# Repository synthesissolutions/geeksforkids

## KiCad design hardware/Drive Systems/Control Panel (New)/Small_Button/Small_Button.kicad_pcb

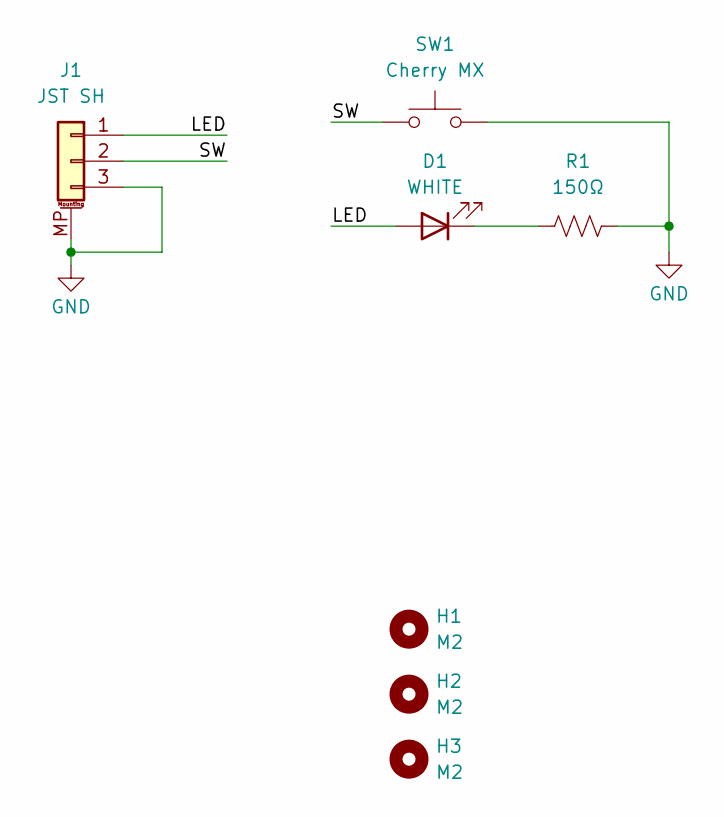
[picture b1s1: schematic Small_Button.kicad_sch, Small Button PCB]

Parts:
D1: WHITE; LED_D3.0mm; MPN C210322
H1, H2, H3: M2; MountingHole_2.2mm_M2_DIN965
J1: JST SH; JST_SH_SM03B-SRSS-TB_1x03-1MP_P1.00mm_Horizontal; MPN C160403
R1: 150Ω; R_0603_1608Metric; MPN C2907103
SW1: Cherry MX; SW_Cherry_MX_1.00u_PCB; MPN C400229

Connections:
/LED: D1.2 (A), J1.1
/SW: J1.2, SW1.1
GND: J1.3, J1.MP (MountPin), R1.2, SW1.2
unnamed: D1.1 (K), R1.1

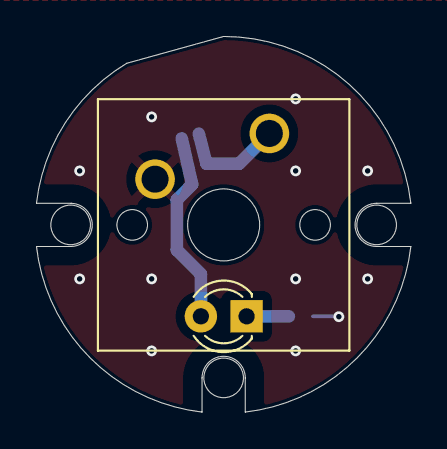
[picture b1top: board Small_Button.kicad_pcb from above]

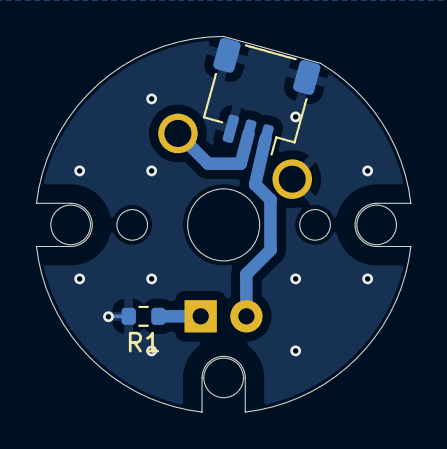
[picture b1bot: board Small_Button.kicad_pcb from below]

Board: 2 copper layers, 20.8 x 20.9 mm, 7 parts (2 on the bottom side), 4 nets.

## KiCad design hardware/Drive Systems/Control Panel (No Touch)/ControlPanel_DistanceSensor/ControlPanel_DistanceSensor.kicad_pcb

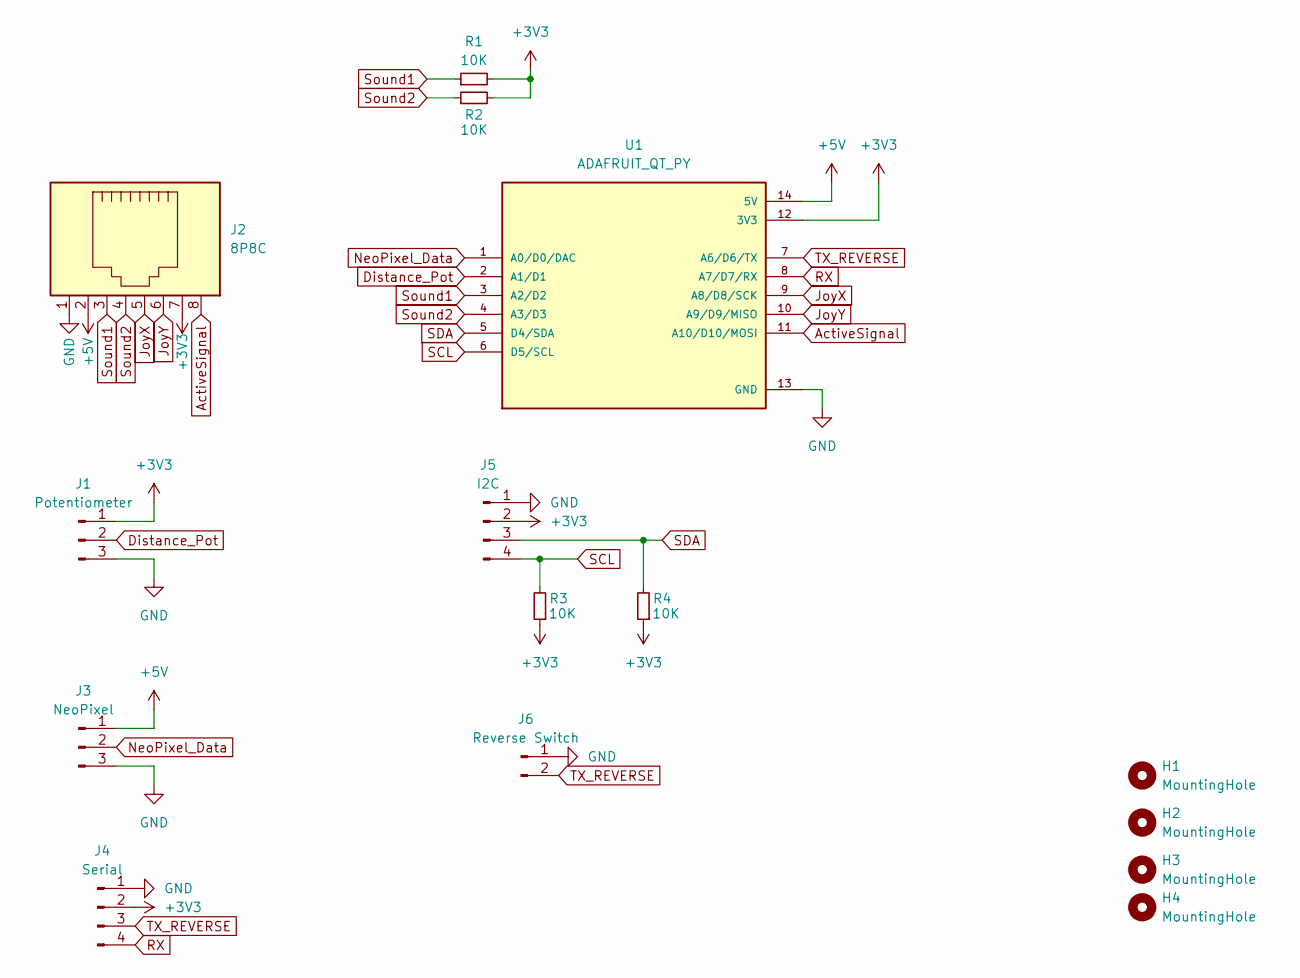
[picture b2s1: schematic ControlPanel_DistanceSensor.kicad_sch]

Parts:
H1, H2, H3, H4: MountingHole; MountingHole_3.2mm_M3
J1: Potentiometer; JST_XH_B3B-XH-A_1x03_P2.50mm_Vertical
J2: 8P8C; RJ45_x08_Tab_Up
J3: NeoPixel; JST_XH_B3B-XH-A_1x03_P2.50mm_Vertical
J4: Serial; JST_XH_B4B-XH-A_1x04_P2.50mm_Vertical
J5: I2C; JST_XH_B4B-XH-A_1x04_P2.50mm_Vertical
J6: Reverse Switch; JST_XH_B2B-XH-A_1x02_P2.50mm_Vertical
R1, R2, R3, R4: 10K; R_Axial_DIN0204_L3.6mm_D1.6mm_P7.62mm_Horizontal
U1: ADAFRUIT_QT_PY; MODULE_ADAFRUIT_QT_PY; PARTREV 2022-12-12

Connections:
+3V3: J1.1, J2.7, J4.2, J5.2, R1.2, R2.2, R3.1, R4.1, U1.12 (3V3)
+5V: J2.2, J3.1, U1.14 (5V)
ActiveSignal: J2.8, U1.11 (A10/D10/MOSI)
Distance_Pot: J1.2, U1.2 (A1/D1)
GND: J1.3, J2.1, J3.3, J4.1, J5.1, J6.1, U1.13 (GND)
JoyX: J2.5, U1.9 (A8/D8/SCK)
JoyY: J2.6, U1.10 (A9/D9/MISO)
NeoPixel_Data: J3.2, U1.1 (A0/D0/DAC)
RX: J4.4, U1.8 (A7/D7/RX)
SCL: J5.4, R3.2, U1.6 (D5/SCL)
SDA: J5.3, R4.2, U1.5 (D4/SDA)
Sound1: J2.3, R1.1, U1.3 (A2/D2)
Sound2: J2.4, R2.1, U1.4 (A3/D3)
TX_REVERSE: J4.3, J6.2, U1.7 (A6/D6/TX)

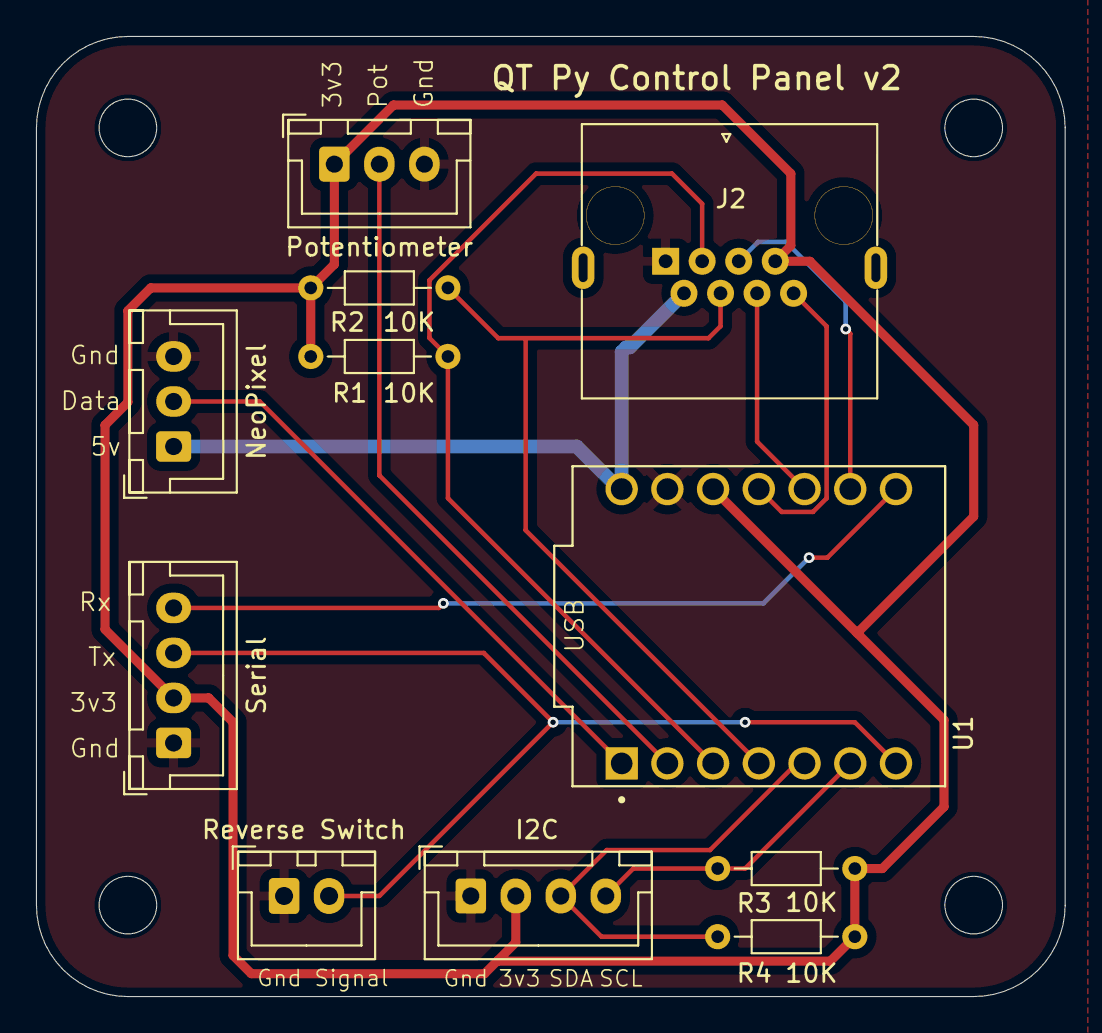
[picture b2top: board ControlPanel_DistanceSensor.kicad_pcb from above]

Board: 2 copper layers, 57.2 x 53.3 mm, 15 parts (0 on the bottom side), 14 nets.

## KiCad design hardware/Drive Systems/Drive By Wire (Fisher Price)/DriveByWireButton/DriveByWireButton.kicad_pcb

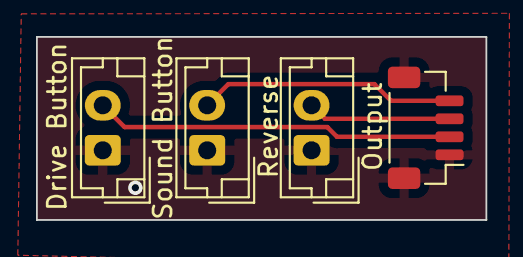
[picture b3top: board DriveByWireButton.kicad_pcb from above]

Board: 2 copper layers, 25.0 x 10.2 mm, 4 parts (0 on the bottom side), 4 nets.

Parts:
J1: Sound Button; JST_EH_B2B-EH-A_1x02_P2.50mm_Vertical
J2: Drive Button; JST_EH_B2B-EH-A_1x02_P2.50mm_Vertical
J3: Reverse; JST_EH_B2B-EH-A_1x02_P2.50mm_Vertical
J4: Output; JST_SH_BM04B-SRSS-TB_1x04-1MP_P1.00mm_Vertical

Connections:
DriveButton: J2.2, J4.2
GND: J1.1, J2.1, J3.1, J4.1, J4.MP
ReverseButton: J3.2, J4.3
SoundButton: J1.2, J4.4

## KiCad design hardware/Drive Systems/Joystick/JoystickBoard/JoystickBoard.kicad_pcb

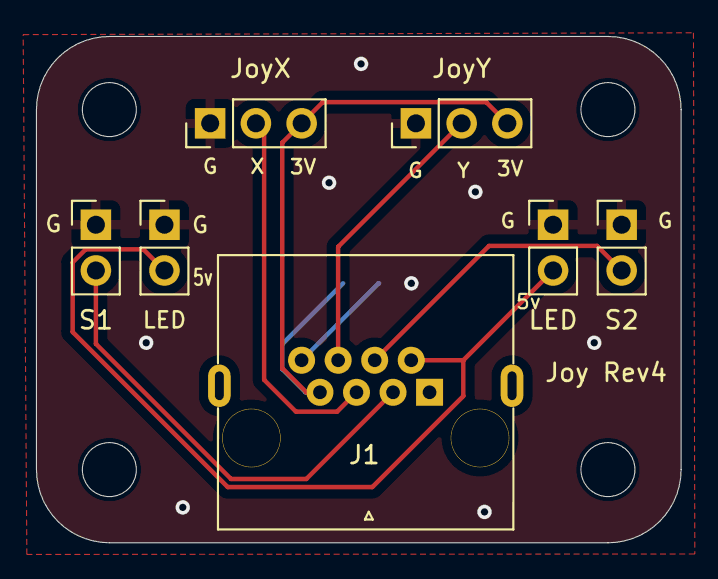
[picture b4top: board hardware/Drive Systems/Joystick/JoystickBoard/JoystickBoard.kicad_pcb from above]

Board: 2 copper layers, 35.8 x 28.1 mm, 12 parts (1 on the bottom side), 8 nets.

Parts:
H1, H2, H3, H4: MountingHole_3mm
J1: 8P8C; RJ45_x08_Tab_Up
J2: S1; PinHeader_1x02_P2.54mm_Vertical
J3: S2; PinHeader_1x02_P2.54mm_Vertical
J4: JoyX; PinHeader_1x03_P2.54mm_Vertical
J5: JoyY; PinHeader_1x03_P2.54mm_Vertical
J6, J7: LED; PinHeader_1x02_P2.54mm_Vertical
R1: 10K; R_0805_2012Metric_Pad1.20x1.40mm_HandSolder

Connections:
+3.3V: J1.7, J4.3, J5.3, R1.2
+5V: J1.2, J6.2, J7.2
GND: J1.1, J2.1, J3.1, J4.1, J5.1, J6.1, J7.1
JoystickX: J1.5, J4.2
JoystickY: J1.6, J5.2
unnamed: J1.8, R1.1
Sound1: J1.3, J2.2
Sound2: J1.4, J3.2

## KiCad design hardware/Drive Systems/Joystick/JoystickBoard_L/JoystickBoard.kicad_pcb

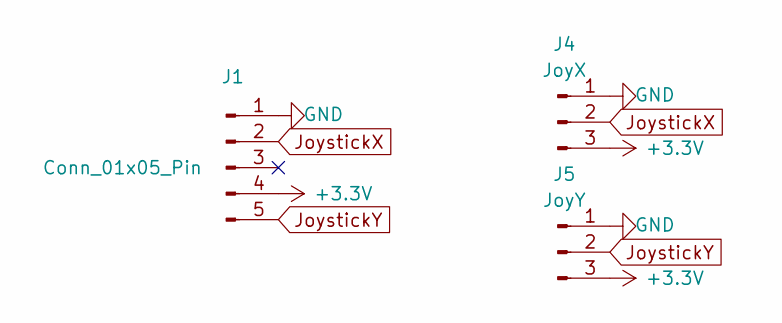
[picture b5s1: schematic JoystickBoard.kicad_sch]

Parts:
J1: Conn_01x05_Pin; JST_XH_B5B-XH-A_1x05_P2.50mm_Vertical
J4: JoyX; Analog_joystick_pot
J5: JoyY; Analog_joystick_pot

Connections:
+3.3V: J1.4, J4.3, J5.3
GND: J1.1, J4.1, J5.1
JoystickX: J1.2, J4.2
JoystickY: J1.5, J5.2

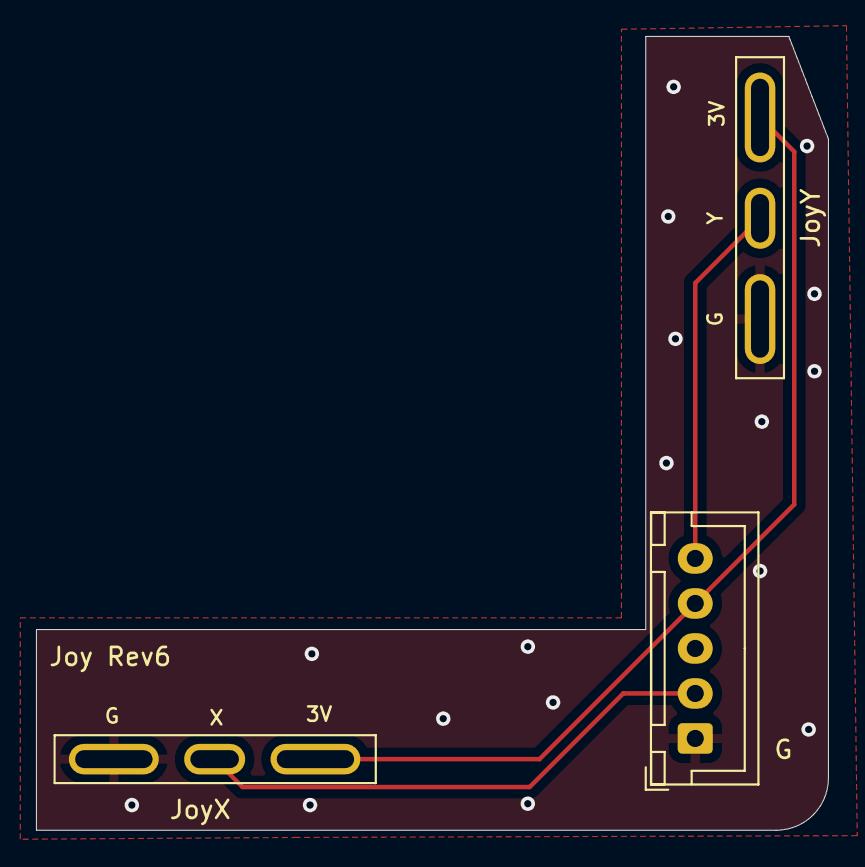
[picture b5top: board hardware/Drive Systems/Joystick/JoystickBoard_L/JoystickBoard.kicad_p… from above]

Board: 2 copper layers, 44.0 x 44.1 mm, 3 parts (0 on the bottom side), 4 nets.

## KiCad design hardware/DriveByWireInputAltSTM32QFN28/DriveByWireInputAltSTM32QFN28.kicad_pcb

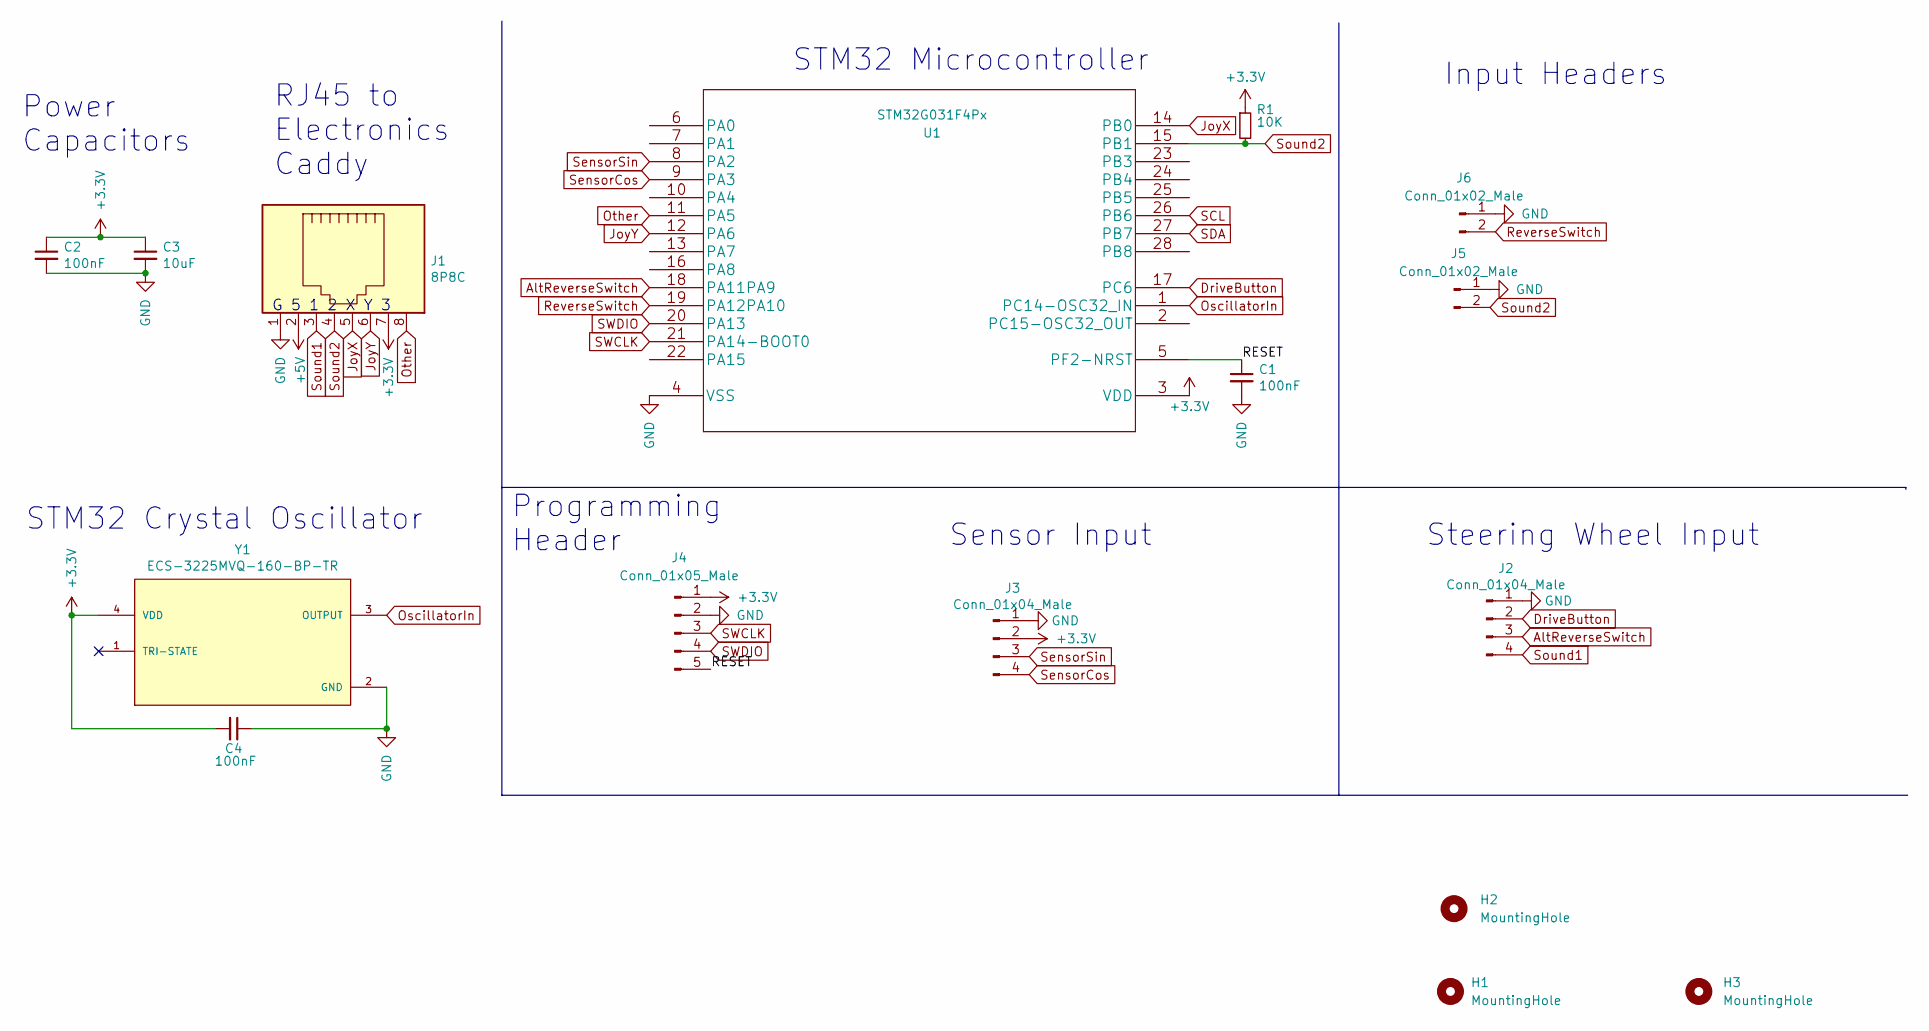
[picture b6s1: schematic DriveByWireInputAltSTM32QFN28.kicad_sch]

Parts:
C1, C2, C4: 100nF; C_0805_2012Metric; MPN C49678
C3: 10uF; C_0805_2012Metric; MPN C15850
H1, H2, H3: MountingHole; MountingHole_3.2mm_M3
J1: 8P8C; RJ45_x08_Tab_Up
J2, J3: Conn_01x04_Male; JST_SH_BM04B-SRSS-TB_1x04-1MP_P1.00mm_Vertical; MPN C145961
J4: Conn_01x05_Male; JST_SH_BM05B-SRSS-TB_1x05-1MP_P1.00mm_Vertical; MPN C2764199
J5, J6: Conn_01x02_Male; JST_XH_B2B-XH-AM_1x02_P2.50mm_Vertical
R1: 10K; R_0805_2012Metric; MPN C17414
U1: STM32G031F4Px; STM32G031G8U6; MPN C432211
Y1: ECS-3225MVQ-160-BP-TR; OSC_ECS-3225MVQ-160-BP-TR; MPN C252336

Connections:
+3V3: C2.1, C3.1, C4.2, J1.7, J3.2, J4.1, R1.1, U1.3 (VDD), Y1.4 (VDD)
+5V: J1.2
/RESET: C1.1, J4.5, U1.5 (PF2-NRST)
AltReverseSwitch: J2.3, U1.18 (PA11PA9)
DriveButton: J2.2, U1.17 (PC6)
GND: C1.2, C2.2, C3.2, C4.1, J1.1, J2.1, J3.1, J4.2, J5.1, J6.1, U1.4 (VSS), Y1.2 (GND)
JoyX: J1.5, U1.14 (PB0)
JoyY: J1.6, U1.12 (PA6)
OscillatorIn: U1.1 (PC14-OSC32_IN), Y1.3 (OUTPUT)
Other: J1.8, U1.11 (PA5)
ReverseSwitch: J6.2, U1.19 (PA12PA10)
SCL: U1.26 (PB6)
SDA: U1.27 (PB7)
SWCLK: J4.3, U1.21 (PA14-BOOT0)
SWDIO: J4.4, U1.20 (PA13)
SensorCos: J3.4, U1.9 (PA3)
SensorSin: J3.3, U1.8 (PA2)
Sound1: J1.3, J2.4
Sound2: J1.4, J5.2, R1.2, U1.15 (PB1)

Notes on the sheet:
Steering Wheel Input
Programming Header
Input Headers
Power Capacitors
STM32 Microcontroller
Sensor Input
RJ45 to Electronics Caddy
G 5 1 2 X Y 3
STM32 Crystal Oscillator

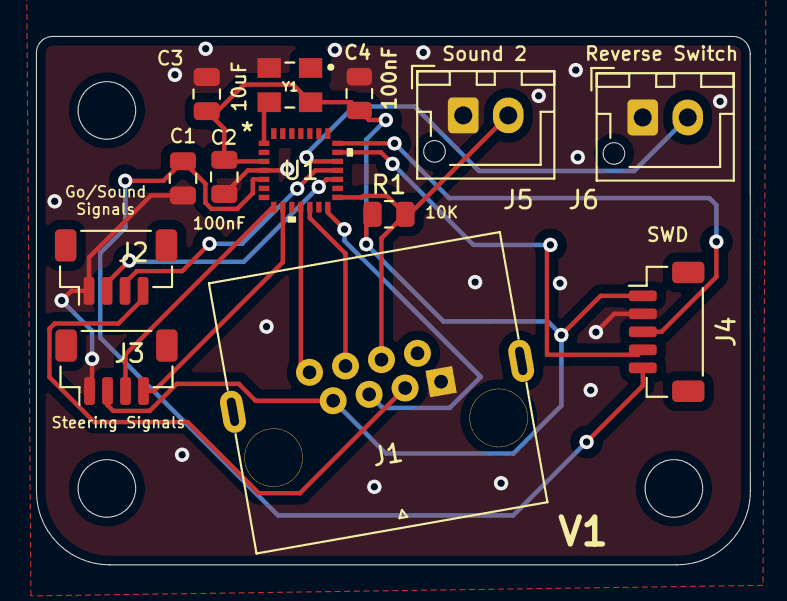
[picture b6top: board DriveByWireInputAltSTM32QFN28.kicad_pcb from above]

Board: 2 copper layers, 39.7 x 29.4 mm, 16 parts (0 on the bottom side), 16 nets.

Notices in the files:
parts and their libraries:
Copyright 2021 Accelerated Designs. All rights reserved.
